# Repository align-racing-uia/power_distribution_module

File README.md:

<h1 align="center"> Power Distribution Module </h1> <br>
<p align="center">
    
</p>

<!-- START doctoc generate TOC please keep comment here to allow auto update -->
<!-- DON'T EDIT THIS SECTION, INSTEAD RE-RUN doctoc TO UPDATE -->
## Table of contents

- [Introduction](#introduction)
- [Align Racing UiA](#alignracinguia)
- [Rules for file structure](#rulesforfilestructure)
- [License](#license)

<!-- END doctoc generated TOC please keep comment here to allow auto update -->

## Introduction

This is the repository for Align Racing's formula student race car's different systems.

## Align Racing UiA

<a href="http://www.alignracing.no/">Align Racing UiA (AR)</a> is a multidisciplinary student organisation at <a href="https://www.uia.no/">The University of Agder (UiA)</a>, that take part in the world’s largest yearly engineering competition; <a href="https://www.imeche.org/events/formula-student">Formula Student (FS)</a>. The organisation continuously consists of around 60 students, from a wide variety of disciplines. The competition includes developing, building, budgeting and marketing a small scale formula type racing car. AR takes this a bit further by having more focus on developing a strong organisation, open for all disciplines, that gives the members a taste of future work-life.

## Rules

## Contribution

## License
All content included in this Git repository is under the license:

Creative Commons Attribution-NonCommercial-ShareAlike 4.0 International

You are free to:
* <b> Share </b> — copy and redistribute the material in any medium or format
* <b> Adapt </b> — remix, transform, and build upon the material

Under the following terms:
* <b> Attribution </b> — You must give appropriate credit, provide a link to the license, and indicate if changes were made. You may do so in any reasonable manner, but not in any way that suggests the licensor endorses you or your use.
* <b> NonCommercial </b> — You may not use the material for commercial purposes.
* <b> ShareAlike </b> — If you remix, transform, or build upon the material, you must distribute your contributions under the same license as the original.
* <b> No additional restrictions </b> — You may not apply legal terms or technological measures that legally restrict others from doing anything the license permits.

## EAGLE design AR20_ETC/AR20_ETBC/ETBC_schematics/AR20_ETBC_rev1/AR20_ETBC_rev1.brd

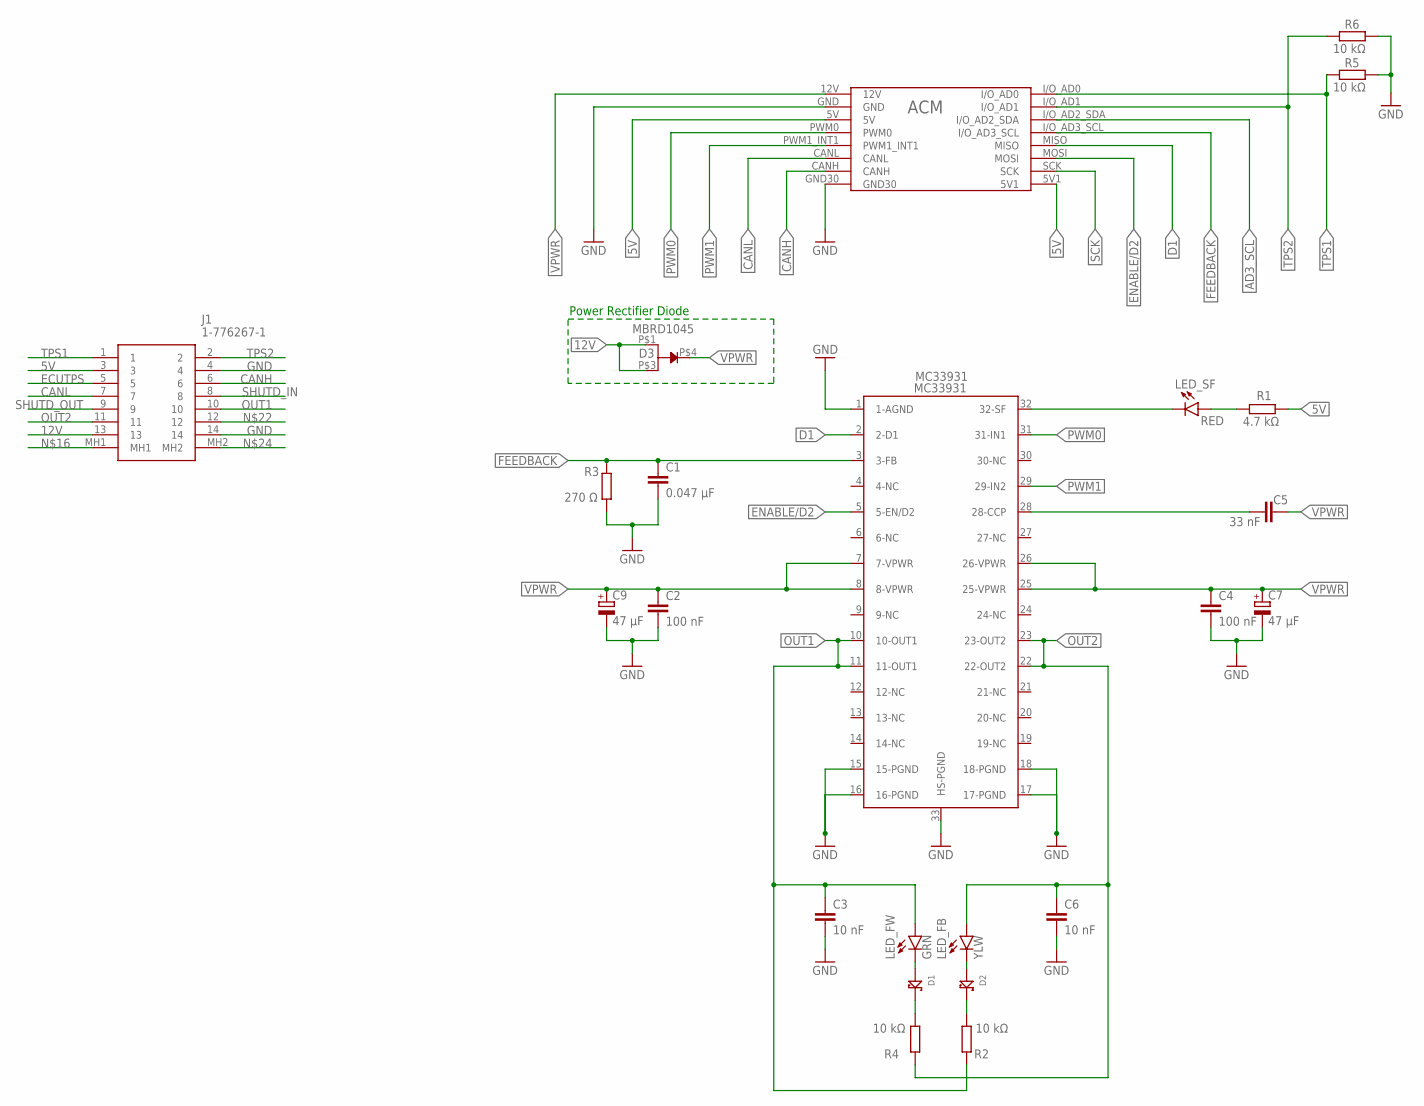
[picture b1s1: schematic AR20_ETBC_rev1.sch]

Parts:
C1: 0.047 μF; C0603
C2, C4: 100 nF; C0603
C3, C6: 10 nF; C0603
C5: 33 nF; C0603
C7, C9: 47 μF; B45181A
D1, D2: CDBU0340-HFCDBU0340-HF; DIOM1709X85
D3: MBRD1045; DPAK
J1: 1-776267-1; 17762671
LED_FB: YLW; SML1206
LED_FW: GRN; SML1206
LED_SF: RED; SML1206
MC33931: MC33931; SOP65P1030X245-33T480X861
R1: 4.7 kΩ; R0603
R2, R4, R5, R6: 10 kΩ; R0603
R3: 270 Ω; R0603
U$3: ACM_CASTELLATED; ACM_CAS_FP

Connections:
5V: J1.3, R1.2, U$3.5V, U$3.5V1
12V: D3.P$1, D3.P$3, J1.13
AD3_SCL: U$3.I/O_AD2_SDA
CANH: J1.6, U$3.CANH
CANL: J1.7, U$3.CANL
D1: MC33931.2 (2-D1), U$3.MISO
ECUTPS: J1.5
ENABLE/D2: MC33931.5 (5-EN/D2), U$3.MOSI
FEEDBACK: C1.1, MC33931.3 (3-FB), R3.2, U$3.I/O_AD3_SCL
GND: C1.2, C2.2, C3.2, C4.2, C6.2, C7.-, C9.-, J1.4, J1.14, MC33931.1 (1-AGND), MC33931.15 (15-PGND), MC33931.16 (16-PGND), MC33931.17 (17-PGND), MC33931.18 (18-PGND), MC33931.33 (HS-PGND), R3.1, R5.2, R6.2, U$3.GND, U$3.GND30
unnamed: LED_SF.A, R1.1
unnamed: LED_SF.C, MC33931.32 (32-SF)
unnamed: D2.2$A (A), LED_FB.C
unnamed: C5.1, MC33931.28 (28-CCP)
unnamed: D1.2$A (A), LED_FW.C
unnamed: D1.1$K (K), R4.1
unnamed: D2.1$K (K), R2.1
OUT1: C3.1, J1.10, LED_FW.A, MC33931.10 (10-OUT1), MC33931.11 (11-OUT1), R2.2
OUT2: C6.1, J1.11, LED_FB.A, MC33931.22 (22-OUT2), MC33931.23 (23-OUT2), R4.2
PWM0: MC33931.31 (31-IN1), U$3.PWM0
PWM1: MC33931.29 (29-IN2), U$3.PWM1_INT1
SCK: U$3.SCK
SHUTD_IN: J1.8
SHUTD_OUT: J1.9
TPS1: J1.1, R5.1, U$3.I/O_AD0
TPS2: J1.2, R6.1, U$3.I/O_AD1
VPWR: C2.1, C4.1, C5.2, C7.+, C9.+, D3.P$4, MC33931.7 (7-VPWR), MC33931.8 (8-VPWR), MC33931.25 (25-VPWR), MC33931.26 (26-VPWR), U$3.12V

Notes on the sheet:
Power Rectifier Diode

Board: 2 copper layers, 23 parts (0 on the bottom side), 22 nets, no tracks yet.

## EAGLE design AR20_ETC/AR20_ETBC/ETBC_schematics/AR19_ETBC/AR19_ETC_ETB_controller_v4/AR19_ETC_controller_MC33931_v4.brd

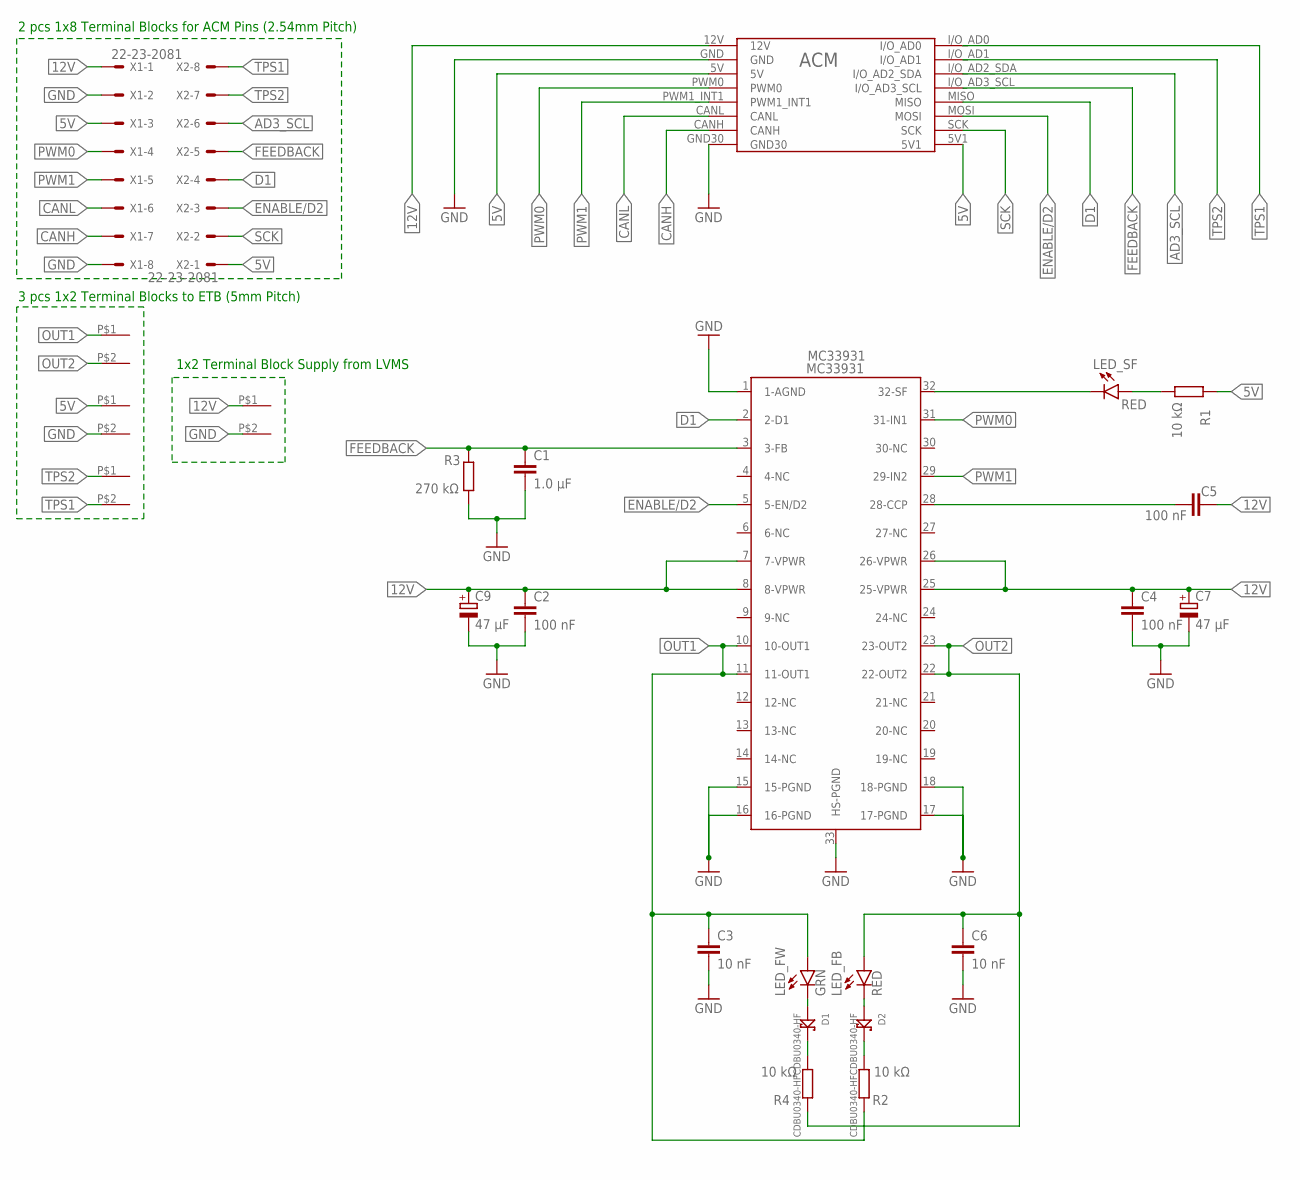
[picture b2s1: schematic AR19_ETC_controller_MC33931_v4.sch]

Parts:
C1: 1.0 μF; C0603
C2, C4, C5: 100 nF; C0603
C3, C6: 10 nF; C0603
C7, C9: 47 μF; B45181A
D1, D2: CDBU0340-HFCDBU0340-HF; DIOM1709X85
LED_FB: RED; SML1206
LED_FW: GRN; SML1206
LED_SF: RED; SML1206
MC33931: MC33931; SOP65P1030X245-33T480X861
R1, R2, R4: 10 kΩ; R0603
R3: 270 kΩ; R0603
U$2, U$5, U$6, U$7: 2PIN_TERMINAL_BLOCK
U$3: ACM_CASTELLATED; ACM_CAS_FP
X1, X2: 22-23-2081

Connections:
5V: R1.2, U$3.5V, U$3.5V1, U$6.P$1, X1.3, X2.1
12V: C2.1, C4.1, C5.2, C7.+, C9.+, MC33931.7 (7-VPWR), MC33931.8 (8-VPWR), MC33931.25 (25-VPWR), MC33931.26 (26-VPWR), U$2.P$1, U$3.12V, X1.1
AD3_SCL: U$3.I/O_AD2_SDA, X2.6
CANH: U$3.CANH, X1.7
CANL: U$3.CANL, X1.6
D1: MC33931.2 (2-D1), U$3.MISO, X2.4
ENABLE/D2: MC33931.5 (5-EN/D2), U$3.MOSI, X2.3
FEEDBACK: C1.1, MC33931.3 (3-FB), R3.2, U$3.I/O_AD3_SCL, X2.5
GND: C1.2, C2.2, C3.2, C4.2, C6.2, C7.-, C9.-, MC33931.1 (1-AGND), MC33931.15 (15-PGND), MC33931.16 (16-PGND), MC33931.17 (17-PGND), MC33931.18 (18-PGND), MC33931.33 (HS-PGND), R3.1, U$2.P$2, U$3.GND, U$3.GND30, U$6.P$2, X1.2, X1.8
unnamed: LED_SF.A, R1.1
unnamed: LED_SF.C, MC33931.32 (32-SF)
unnamed: D2.2$A (A), LED_FB.C
unnamed: C5.1, MC33931.28 (28-CCP)
unnamed: D1.2$A (A), LED_FW.C
unnamed: D1.1$K (K), R4.1
unnamed: D2.1$K (K), R2.1
OUT1: C3.1, LED_FW.A, MC33931.10 (10-OUT1), MC33931.11 (11-OUT1), R2.2, U$5.P$1
OUT2: C6.1, LED_FB.A, MC33931.22 (22-OUT2), MC33931.23 (23-OUT2), R4.2, U$5.P$2
PWM0: MC33931.31 (31-IN1), U$3.PWM0, X1.4
PWM1: MC33931.29 (29-IN2), U$3.PWM1_INT1, X1.5
SCK: U$3.SCK, X2.2
TPS1: U$3.I/O_AD0, U$7.P$2, X2.8
TPS2: U$3.I/O_AD1, U$7.P$1, X2.7

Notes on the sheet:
2 pcs 1x8 Terminal Blocks for ACM Pins (2.54mm Pitch)
3 pcs 1x2 Terminal Blocks to ETB (5mm Pitch)
1x2 Terminal Block Supply from LVMS

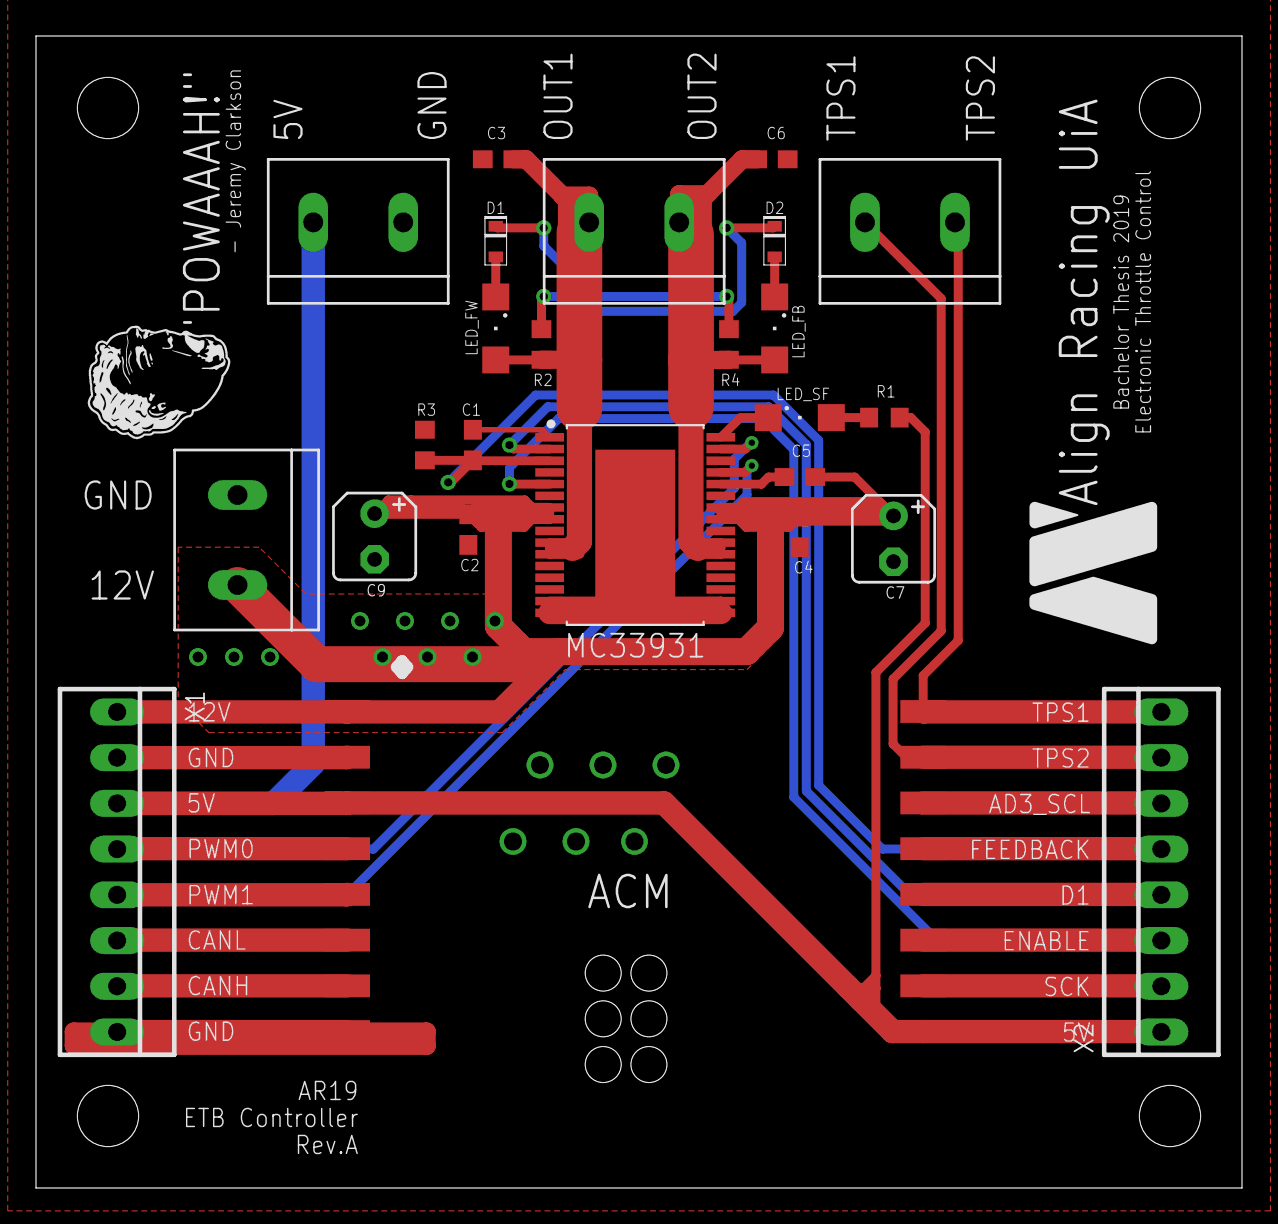
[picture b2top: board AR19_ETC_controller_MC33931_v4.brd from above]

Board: 2 copper layers, 67.0 x 64.0 mm, 25 parts (0 on the bottom side), 23 nets.

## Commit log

2019-06-10 Added: AR Info
2019-06-10 Added: AR19-ACM
2019-06-10 Fix: Year updated
2019-06-10 Added: ACM 2019 md file
2019-06-10 Added: ACM 2019 Documentation
2019-07-24 First design of ACM2020
2019-07-24 First design of ACM2020 - 2
2019-07-25 Added MCP25625 and PDFS
2019-07-26 See change log for update.
2019-07-27 Changelog for 27.07.2019
2019-07-28 Changelog for 28.07.2019
2019-07-29 Changelog for 29.07.2019
2019-07-30 Changelog for 30.07.2019
2019-08-02 Lagt til ASL
2019-08-04 Changelog for 03.08.2019
2019-08-04 Changelog for 04.08.2019
2019-08-11 3D Export
2019-10-06 Changelog for 06.10.2019
2019-10-20 First sketch of the pdm
    Rough sketch of first e-fuse switch, phase1
2019-10-22 CPU template
    Added cpu-rtos template
2019-10-22 readme added
    A temporary readme file added
2019-10-29 Can Controlling thread
    Added, it compiles other threads work Bu I haven't tested the can controller it self.
    Also added a Serial interface.
2019-10-30 Refining pdm schematics
2019-10-30 Refining pdm phase 1
2019-10-30 Added voltage divider KiCAd
2019-10-30 PDM Phase 1 mostly complete
2019-10-30 Functional Can Test program
2019-11-04 Added: Wire resistance calculation
2019-11-05 Added: Todo, and Thermal radiation formula
2019-11-06 Added Brakelight
2019-11-06 PCB VD finished
2019-11-06 Redigert
2019-11-06 CAN Fix
2019-11-06 Brakelight Shematic 95% ready.
2019-11-06 Added: Stefan-Boltzmann Law (Black body)
2019-11-07 Brakelight PCB 50% ready
2019-11-07 Brakelight 80% Ready
2019-11-07 Added Youtube video
2019-11-08 Added: Convection and Radiation formulas
2019-11-11 Pdm test code
2019-11-11 Auto stash before rebase of "master"
2019-11-13 PDM: VOL1 + Breakout board
2019-11-18 Separated chematics, and brakout board into two separate folders
2019-11-18 Moved footprints, and libraries in separate folders.
2019-11-18 Revert "Moved footprints, and libraries in separate folders."
    This reverts commit ce8c3de0d6cd9b7318d398a4fba87650c9fee54b.
2019-11-18 Copied symbol library into breakout board project
2019-11-18 PDM breakout boards and gerber files
2019-11-20 Small trace adjustments.
2019-11-21 Added alert to inversion to test code
2019-11-24 First draft of Gear phase, shutdown relays, and Direct phases.
2019-11-24 Added label on mosfets, added fuel pump sinking output
2019-11-28 Major update to testcode
    - Set up for visual studio code
    - Re organized structure
    - created INA233 objects
    - Made object oriented structure
2019-12-03 Current limit, alert set and monitoring, minor restructuring
    -New functions for current limit and alert
    -New structs for data, and settings configuration.
    -function for transmitting
    -not all functions are in use, work in progress....
    -a lot of temporary testing stuff.
2019-12-04 New transmit functions, line voltage reading
    - added send transmit function to cleanup code
    - added send transmit function to cleanup code
    - implemented line voltage reading.
2019-12-06 voltage_L reading, ADC settings
2019-12-18 Under/over voltage limits, and further testing
2020-01-08 Major Schematics changes-work in progress
    - Added rest of the phases
    - Corrected pin names, and began to connect everything
    - Began mapping the connectors, Pin-out not yet verified for all connectors
    - Began mapping of user interface (Led indicators)
    - INA233 now senses OUT voltage on mosfets instead of main 12Volt
    - Added extra decoupling capacitors
2020-01-10 Added LEDs and switches.
    - Added all status leds
    - Added all switches
    - ! Connections are work in progress, not everything is correct
2020-01-11 Fixed wrong value components and ports, wiring, see discription
    - Fixed supply cappacitor value 220 nf to 100nf
    - Fixed IN cappacitor value 220 nf to 150 nf
    - Fixed out cappacitor value, 220nf to 10 nf
    - Made a mux for mosfet sense
    - Found a I/O port expander
    - Added some and removed some leds
2020-01-13 Fixed issues, controlled components, BOM, see discription
    - added acm symbol
    - fixed wrongly faced P-mosfets
    - I/O expander now sinks led instead of source
    - Bill of material mostly done
    - Correct address for INA233 chips.
    - Now 4 diodes serves as flyback for all mosfets
2020-01-19 PCB design, and issue fixing, work in progress
    - Error fixed: Mux mosfet resistor change to ground
    - Open drain output added on phase 6, for engine blipping purpose
    - Most of pcb symbols and footprints are finished, including main connector
    - PCB is change from 1oz to 2oz copper layer, for easier routing.
    - Basic Draft of pcb is done, for now.
2020-01-19 PCB design, and misc, see description, work in progress
    - added shutdown circuit for ACM shutdown capability
    PCB layout, in progress:
    - added copper pour for 12 volt, for fuses
    - arranged indicator LED's
    - arranged some of the P1-P7 caps and resistors
    - re arranged P1-p7 in ascending order.
2020-01-20 PCB Design, Work in progress
2020-01-20 PCB Design, minor schematics changes, work in progress, see description
    - Removed mos sense caps and resistors accept one,
    since only one measurement can be done, at a time.
    - added mos sens protection resistors on each line, to protect mux mosfets and micro controller.
    - Routing plan mostly finalized, some of the traces are just proof of concept.
    those needs to be routed nicely.
2020-01-22 First Complete Draft of PCB and schematics, - minus see discription
    - missing correct smd switch header
    - missing correct main power plug
    - tweeks still needs to be done
    - Extra inspection of schematics pending
    - proper, in depth quiality controll of pcb work pending
2020-01-23 DRC, work Fixed couple of unconnected items
    - Main power connection is still missing
    - Button connector still missing
2020-01-26 Finilizing the desing, some few missing components
    - Increased the size to accommodate mounting holes
    - Fixed wrong p mos pin out, due to wrong schematics drawing
    - Done alot of tweeeks
    - Button connector still missing.
2020-01-28 Alpha version DONE! - Gerber files generated
    - Tweeked
    - checked and re cheked
    - added all missing components
    - Created a really nice silkscreen
    - Ready To Test
2020-01-29 Fixed wrong resistors, mos sense. Gerber files updated
    - removed all R_is_protection resistors on each mosfet line
    - added one R_is_protection resistors to mos_sense_all
    ps, mux N-fets, does not need overvoltage protection. 60 volt tolerant.
2020-01-29 Calculated and changes i2c pullup Resistors to 2 K
2020-01-30 Small tweaks, complete 3d render in ki-cad
    - change switch pin with phase 1 enable, on the mcu, to get phase 1 PWM
    switch can now be sampled with change interrupt.
    - couple of traces beautified
2020-01-30 Gerber zip name change
2020-01-30 Solidworks 3d model, almost complete.
    - missing decal, on the back side
2020-02-01 Generated new gerberfile, with forgotten solder mask
2020-02-26 PDM Testing on the real PCB, Critical bugs found
    working on PDM Improvmente and bugs list,
2020-02-29 Updated list of improvements
2020-03-03 PDM testint, port expander, hard coded atm.
2020-03-05 This marks end of Alpha version and Beginning of BETA.
    - All relevant test of PDM completed,
    - Improvement and error list generated.
2020-03-06 Major redesign. schematics completed, PCB work in progress
    -TODO : A proper changelog file. Where all changes will apear
    - Redesigned schematics to accommodate errors in the improvement list
    - More detail in ALPHA improvement list
2020-03-07 All components in place - PCB work in progress
2020-03-08 Pdm version B Draft finished
2020-03-09 misc silkscreen changes
2020-03-09 Gerber files generated, fixed diode footprint, added misc silkscreen
2020-03-09 Generated Zip
2020-03-10 End of Beta beginning of Charlie.
    - RE0.2mm rework, jlc pcb minimum clearance with 2 OZ copper, was not advertised, properly
    a retrace
    Re positioning of some of components
    added temp sensor
2020-04-19 Further testing, reveals pdm needs rework
    - As of now, there are major errors in schematics.
    - Needs rework. Version charlie postponed.
    - Very nice pcb layout thats almost finished.
    worth noting this layout for the future
2020-06-17 Further testing, reveals pdm needs rework, also really nice layout.
    - As of now, there are major errors in schematics.
    - Needs rework. Version charlie postponed.
    - Very nice pcb layout thats almost finished.
    worth a note for the future
2020-06-17 schematics rework
    Fixed INA233 frying due to inductive flyback:
    - Paced ina233 high side of the mosftets
    - New input protection reseistors, and zener diodes, on each ina233.
    Simplified:
    - Removed the MUX and mos sense lines, as i realize that most of this functionality can be obtained trough INA233.
    - Removed some of the cappacitors , besides the most needed ones.
2020-06-22 Working on pcb layout
2020-08-06 PDM mostly complete
    - Reverse polarity protection implemented
    - All traces layed out
    - final polish missing
    - DRC missing
    - Final check missing
2020-08-07 Drc work
    Wrong footprint, all else in DRC is good.
2020-08-08 Fixed a GND trace bug, where trace s accidentaly set to 0.2, DRC work
2020-08-10 Mostly finalized
    - Fixed alot of the masking
    - Replaced main Flyback diodes to shotky type with low VF
    - Fix DRC one footprint still to small clearance
    - Fix silkscreen
2020-08-11 All done except port expander footprint
2020-08-12 PDM V 3 Charlie Finished, awaiting final inspection
2020-08-22 Gerber files generated, directory cleaned
2020-08-22 Deleted old gerber zip and generated new zip.
2020-08-22 Re made gerber files
2020-08-22 Re made gerber files, beware gerber options reset each time
2020-08-22 Added shutdown circuit monitoring, new gerber files
2020-08-22 A litte fix in the shutdown monitoring, new gerber files
2020-08-23 shematics adjustments, and fixing values and names
2020-08-24 Rename zip and deleted "Nylund"-folder
2020-08-24 Gerber generated wrongly, Regenerated gerber files
2020-09-13 Cleanup Deleted everything than PDM in PDM Branch
2020-09-15 Minor Coding
2020-09-18 Edited Platformio.ini
    - Chose a correct mcu
2020-09-18 Minor edit
2020-12-19 Created Atmel Studio Project, working readback check
2021-01-03 Changer Led Resistor Values
2021-02-06 Changes to sketch
    Cleaned up sketch and readied for new fuctions
2021-02-06 Fixed several errors, updated implementation
    Fixed several syntax errors, made implementation of INA233 1-7 better, properly implemented objects for the mosfets. Also updated Arduinocore folder to not have build errors
2021-02-07 Minor changes
    Commented out sections for easier debugging and reading, added more instances of INA233 and mosfets
2021-03-10 Made new atmel project with CAN included, USE PDM_wCAN
    Created new project to avoid include issues, also more appropriately named foldres/files. Old project still included but it currently has build issues due to the CAN library. Use PDM_wCAN from now on
2021-03-20 Blinkling LED working
    Blue LED connected to mosfet P4, P1-P7 doesn't work with load connected
2021-03-27 Commented out CAN code
    for debugging
2021-03-27 Fixed pinmodes
2021-03-27 Minor changes
2021-04-03 Functional with CAN
    Turning off mosfets with CAN works, INA233 sends back correct values over CAN, fixed minor issue with testcommunication using wrong command
2021-05-16 Smiplified PDM design, but still "Snasen"
    Performs all the required duties of a PDM, in a simple and reliable manner. Without the complicated and "Fancy" stuff.
    - Regular automotive blade fuses
    - No digital monitoring
    - Analog user interface
    - No buttons or dip switches.
    - Aux is still present, works in conjunction with ACM.
2021-08-01 Directory refactoring and README.md adjustment.
